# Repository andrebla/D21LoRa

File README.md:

# D21LoRa

A simple circuit to integrate a LoRa transceiver, an OLED display, and a SD card to an Atmel ATSAMD21 microcontroller

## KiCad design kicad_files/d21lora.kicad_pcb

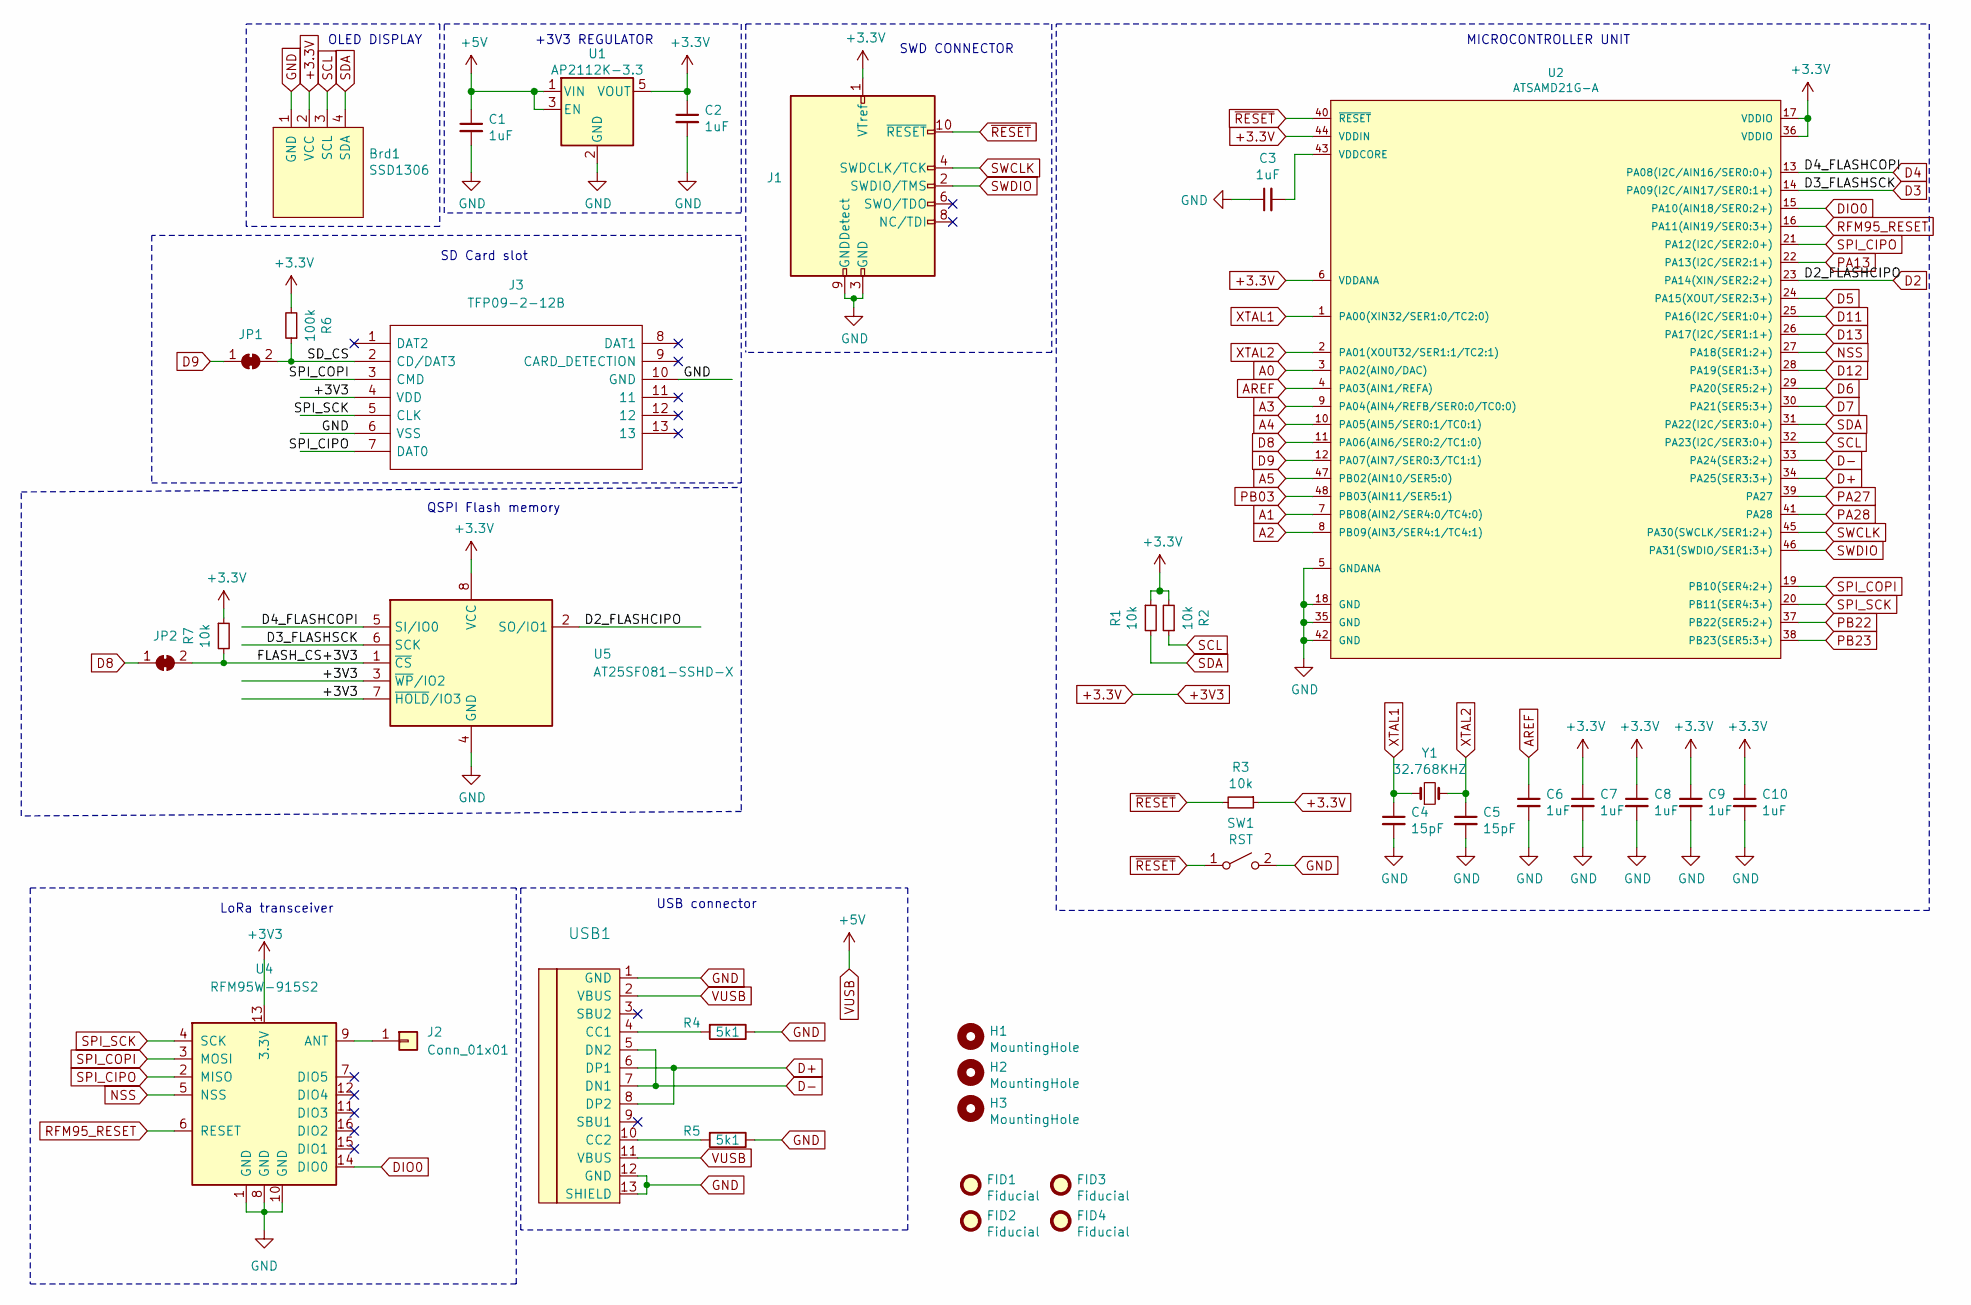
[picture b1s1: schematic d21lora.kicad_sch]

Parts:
Brd1: SSD1306; 128x64OLED
C1, C2, C3, C6, C7, C8, C9, C10: 1uF; C_0603_1608Metric
C4, C5: 15pF; C_0603_1608Metric
FID1, FID2, FID3, FID4: Fiducial; Fiducial_0.5mm_Mask1mm
H1, H2, H3: MountingHole; MountingHole_3.2mm_M3
J1: Conn_ARM_JTAG_SWD_10; IDC-Header_2x05_P2.54mm_Vertical
J2: Conn_01x01; PinHeader_1x01_P2.54mm_Vertical
J3: TFP09-2-12B; TFP09212B; Manufacturer_Part_Number TFP09-2-12B
JP1, JP2: SolderJumper_2_Bridged; SolderJumper-2_P1.3mm_Bridged_RoundedPad1.0x1.5mm
R1, R2, R3, R7: 10k; R_0603_1608Metric
R4, R5: 5k1; R_0603_1608Metric
R6: 100k; R_0603_1608Metric
SW1: RST; SW_SPST_FSMSM
U1: AP2112K-3.3; SOT-23-5
U2: ATSAMD21G-A; TQFP-48_7x7mm
U4: RFM95W-915S2; HOPERF_RFM9XW_SMD
U5: AT25SF081-SSHD-X; SOIC-8_3.9x4.9mm_P1.27mm
USB1: HRO-TYPE-C-31-M-12
Y1: 32.768KHZ; Crystal_SMD_G8-2Pin_3.2x1.5mm

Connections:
+3.3V: Brd1.2 (VCC), C2.1, C7.1, C8.1, C9.1, C10.1, J1.1 (VTref), J3.4 (VDD), R1.1, R2.2, R3.1, R6.2, R7.1, U1.5 (VOUT), U2.6 (VDDANA), U2.17 (VDDIO), U2.36 (VDDIO), U2.44 (VDDIN), U4.13 (3.3V), U5.3 (~WP/IO2), U5.7 (~HOLD/IO3), U5.8 (VCC)
/FLASH_CS+3V3: JP2.2 (B), R7.2, U5.1 (~CS)
/SD_CS: J3.2 (CD/DAT3), JP1.2 (B), R6.1
A0: U2.3 (PA02(AIN0/DAC))
A1: U2.7 (PB08(AIN2/SER4:0/TC4:0))
A2: U2.8 (PB09(AIN3/SER4:1/TC4:1))
A3: U2.9 (PA04(AIN4/REFB/SER0:0/TC0:0))
A4: U2.10 (PA05(AIN5/SER0:1/TC0:1))
A5: U2.47 (PB02(AIN10/SER5:0))
AREF: C6.1, U2.4 (PA03(AIN1/REFA))
D2: U2.23 (PA14(XIN/SER2:2+)), U5.2 (SO/IO1)
D3: U2.14 (PA09(I2C/AIN17/SER0:1+)), U5.6 (SCK)
D4: U2.13 (PA08(I2C/AIN16/SER0:0+)), U5.5 (SI/IO0)
D5: U2.24 (PA15(XOUT/SER2:3+))
D6: U2.29 (PA20(SER5:2+))
D7: U2.30 (PA21(SER5:3+))
D8: JP2.1 (A), U2.11 (PA06(AIN6/SER0:2/TC1:0))
D9: JP1.1 (A), U2.12 (PA07(AIN7/SER0:3/TC1:1))
D11: U2.25 (PA16(I2C/SER1:0+))
D12: U2.28 (PA19(SER1:3+))
D13: U2.26 (PA17(I2C/SER1:1+))
D+: U2.34 (PA25(SER3:3+)), USB1.6 (DP1), USB1.8 (DP2)
D-: U2.33 (PA24(SER3:2+)), USB1.5 (DN2), USB1.7 (DN1)
DIO0: U2.15 (PA10(AIN18/SER0:2+)), U4.14 (DIO0)
GND: Brd1.1 (GND), C1.2, C2.2, C3.1, C4.2, C5.2, C6.2, C7.2, C8.2, C9.2, C10.2, J1.3 (GND), J1.5 (GND), J1.9 (GNDDetect), J3.6 (VSS), J3.10 (GND), R4.1, R5.1, SW1.2 (B), U1.2 (GND), U2.5 (GNDANA), U2.18 (GND), U2.35 (GND), U2.42 (GND), U4.1 (GND), U4.8 (GND), U4.10 (GND), U5.4 (GND), USB1.1 (GND), USB1.12 (GND), USB1.13 (SHIELD)
NSS: U2.27 (PA18(SER1:2+)), U4.5 (NSS)
unnamed: C3.2, U2.43 (VDDCORE)
unnamed: J2.1, U4.9 (ANT)
unnamed: R4.2, USB1.4 (CC1)
unnamed: R5.2, USB1.10 (CC2)
PA13: U2.22 (PA13(I2C/SER2:1+))
PA27: U2.39 (PA27)
PA28: U2.41 (PA28)
PB03: U2.48 (PB03(AIN11/SER5:1))
PB22: U2.37 (PB22(SER5:2+))
PB23: U2.38 (PB23(SER5:3+))
RFM95_RESET: U2.16 (PA11(AIN19/SER0:3+)), U4.6 (RESET)
SCL: Brd1.3 (SCL), R2.1, U2.32 (PA23(I2C/SER3:0+))
SDA: Brd1.4 (SDA), R1.2, U2.31 (PA22(I2C/SER3:0+))
SPI_CIPO: J3.7 (DAT0), U2.21 (PA12(I2C/SER2:0+)), U4.2 (MISO)
SPI_COPI: J3.3 (CMD), U2.19 (PB10(SER4:2+)), U4.3 (MOSI)
SPI_SCK: J3.5 (CLK), U2.20 (PB11(SER4:3+)), U4.4 (SCK)
SWCLK: J1.4 (SWDCLK/TCK), U2.45 (PA30(SWCLK/SER1:2+))
SWDIO: J1.2 (SWDIO/TMS), U2.46 (PA31(SWDIO/SER1:3+))
VUSB: C1.1, U1.1 (VIN), U1.3 (EN), USB1.2 (VBUS), USB1.11 (VBUS)
XTAL1: C4.1, U2.1 (PA00(XIN32/SER1:0/TC2:0)), Y1.1
XTAL2: C5.1, U2.2 (PA01(XOUT32/SER1:1/TC2:1)), Y1.2
~RESET: J1.10 (~RESET), R3.2, SW1.1 (A), U2.40 (~RESET)

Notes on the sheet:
LoRa transceiver
OLED DISPLAY
QSPI Flash memory
SD Card slot
+3V3 REGULATOR
USB connector
SWD CONNECTOR
MICROCONTROLLER UNIT

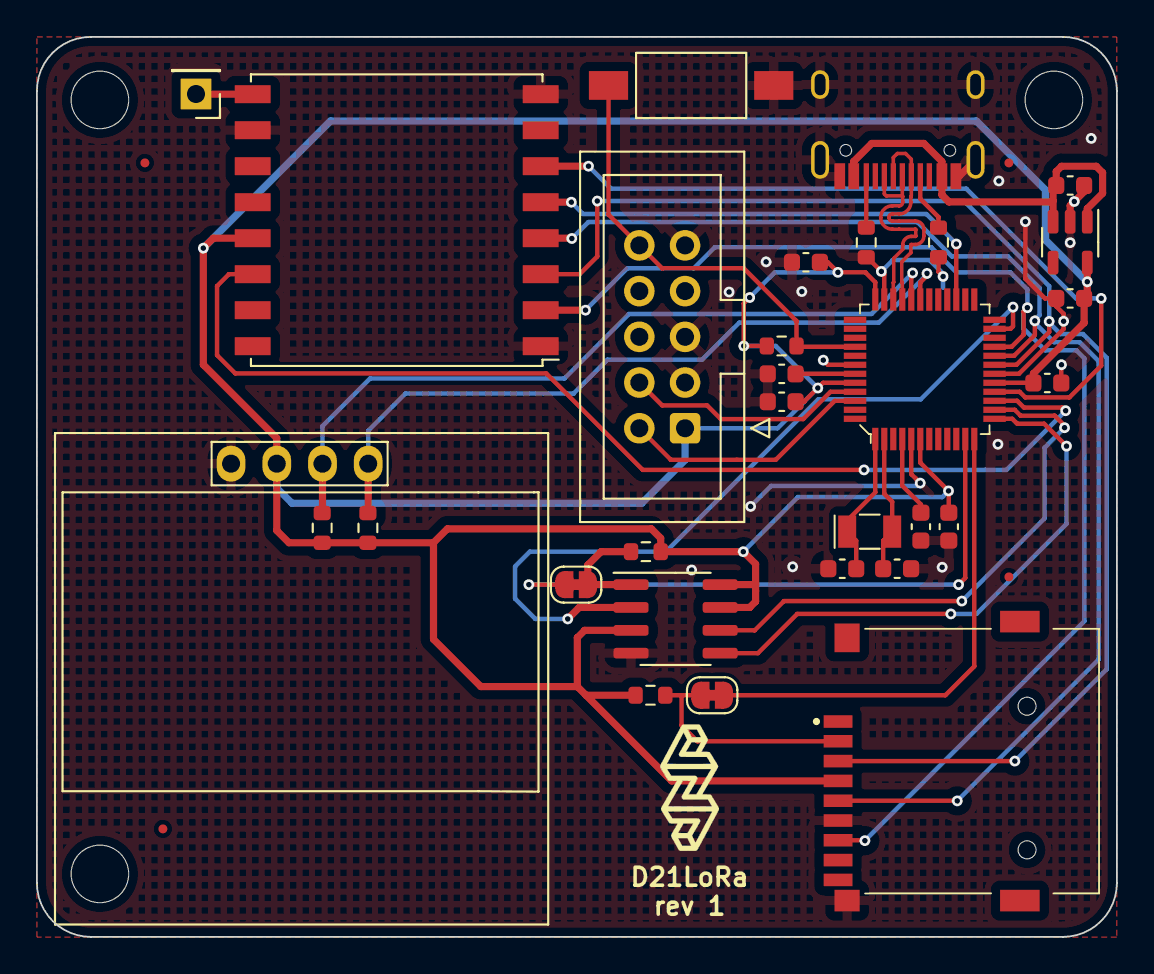
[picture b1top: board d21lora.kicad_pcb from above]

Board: 2 copper layers, 60.0 x 50.0 mm, 37 parts (0 on the bottom side), 30 nets.
